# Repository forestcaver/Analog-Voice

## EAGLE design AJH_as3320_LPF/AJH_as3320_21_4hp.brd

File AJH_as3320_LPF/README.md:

# 3320 LPF

Built and tested

CC-BY-NC-SA 4.0

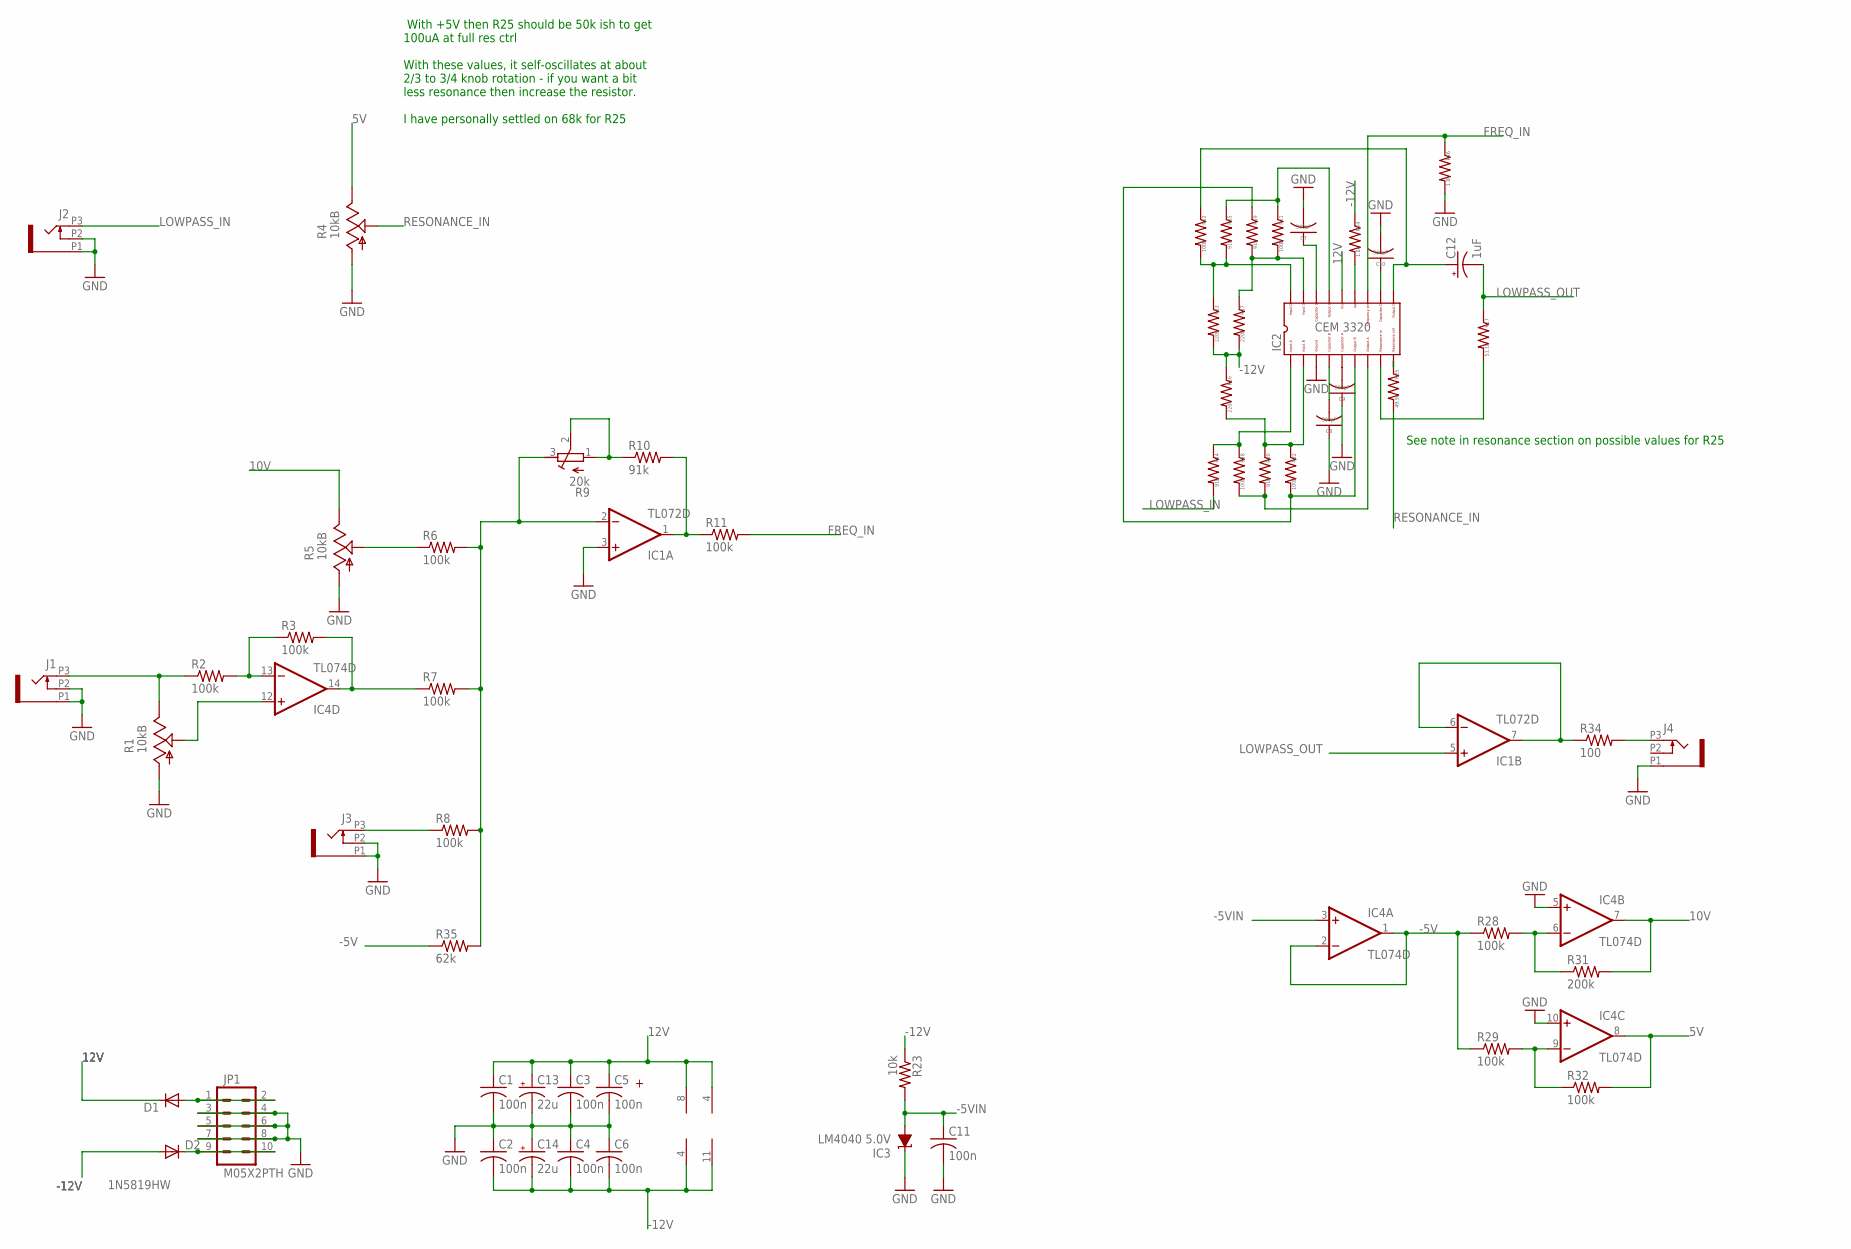
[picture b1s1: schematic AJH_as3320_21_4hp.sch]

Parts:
C1, C2, C3, C4, C5, C6, C11: 100n; C0603
C7, C8, C9, C10: 300pF; C0603
C12: 1uF; PANASONIC_B
C13, C14: 22u; PANASONIC_B
D1, D2: 1N5819HW; SOD123
IC1: TL072D; SO08
IC2: CEM3320QFN24; QFN24
IC3: LM4040 5.0V; DBZ_R-PDSO-G3
IC4: TL074D; SO14
J1, J2, J3, J4: PJ301_THONKICONN6; WQP_PJ_301M6
JP1: M05X2PTH; AVR_ICSP
R1, R4, R5: 10kB; ALPS_POT_VERTICAL
R2, R3, R6, R7, R8, R11, R12, R18, R21, R22, R28, R29, R32: 100k; R0603
R9: 20k; RTRIM3296X
R10, R14, R15, R19, R20: 91k; R0603
R13, R16, R17: 220k; R0603
R23: 10k; R0603
R24, R26: 1.8k; R0603
R25: 49.9k; R0603
R27: 51.1k; R0603
R31: 200k; R0603
R34: 100; R0603
R35: 62k; R0603

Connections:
5V: IC4.8 (OUT), R4.P$1 (E), R32.2
10V: IC4.7 (OUT), R5.P$1 (E), R31.2
12V: C1.1, C3.1, C5.1, C13.+, D1.C, IC1.8 (V+), IC2.P$22 (14), IC4.4 (V+)
-5V: IC4.1 (OUT), IC4.2 (-IN), R28.1, R29.1, R35.1
-5VIN: C11.1, IC3.2 (A), IC4.3 (+IN), R23.2
-12V: C2.2, C4.2, C6.2, C14.-, D2.A, IC1.4 (V-), IC4.11 (V-), R13.2, R16.1, R17.2, R23.1, R24.1
FREQ_IN: IC2.P$19 (12), R11.2, R26.1
GND: C1.2, C2.1, C3.2, C4.1, C5.2, C6.1, C7.2, C8.1, C9.1, C10.2, C11.2, C13.-, C14.+, IC1.3 (+IN), IC2.P$7 (3), IC3.1 (C), IC4.5 (+IN), IC4.10 (+IN), J1.P1 (1), J1.P2 (2), J2.P1 (1), J2.P2 (2), J3.P1 (1), J3.P2 (2), J4.P1 (1), JP1.3, JP1.4, JP1.5, JP1.6, JP1.7, JP1.8, R1.P$3 (A), R4.P$3 (A), R5.P$3 (A), R26.2
LOWPASS_IN: J2.P3 (3), R14.2
LOWPASS_OUT: C12.-, IC1.5 (+IN), R27.1
unnamed: IC1.6 (-IN), IC1.7 (OUT), R34.1
unnamed: IC2.P$3 (18), R12.2, R13.1, R15.2
unnamed: IC4.12 (+IN), R1.P$2 (S)
unnamed: R5.P$2 (S), R6.1
unnamed: IC4.13 (-IN), R2.2, R3.1
unnamed: D1.A, JP1.1, JP1.2
unnamed: IC1.2 (-IN), R6.2, R7.2, R8.2, R9.3 (A), R35.2
unnamed: IC1.1 (OUT), R10.2, R11.1
unnamed: J3.P3 (3), R8.1
unnamed: J4.P3 (3), R34.2
unnamed: IC4.14 (OUT), R3.2, R7.1
unnamed: IC4.9 (-IN), R29.2, R32.1
unnamed: IC4.6 (-IN), R28.2, R31.1
unnamed: D2.C, JP1.9, JP1.10
unnamed: C7.1, IC2.P$24 (16)
unnamed: C8.2, IC2.P$8 (4)
unnamed: C9.2, IC2.P$9 (5)
unnamed: C10.1, IC2.P$17 (11)
unnamed: IC2.P$15 (9), R25.1
unnamed: IC2.P$4 (1), R14.1, R18.1
unnamed: IC2.P$12 (7), R18.2, R20.2
unnamed: IC2.P$11 (6), R19.1, R22.2
unnamed: IC2.P$23 (15), R15.1, R21.1
unnamed: C12.+, IC2.P$16 (10), R12.1
unnamed: IC2.P$14 (8), R27.2
unnamed: IC2.P$5 (2), R16.2, R20.1, R22.1
unnamed: IC2.P$2 (17), R17.1, R19.2, R21.2
unnamed: IC2.P$20 (13), R24.2
unnamed: R9.1 (E), R9.2 (S), R10.1
unnamed: J1.P3 (3), R1.P$1 (E), R2.1
RESONANCE_IN: R4.P$2 (S), R25.2

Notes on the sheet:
With +5V then R25 should be 50k ish to get 100uA at full res ctrl With these values, it self-oscillates at about 2/3 to 3/4 knob rotation - if you want a bit less resonance then increase the resistor. I have personally settled on 68k for R25
See note in resonance section on possible values for R25

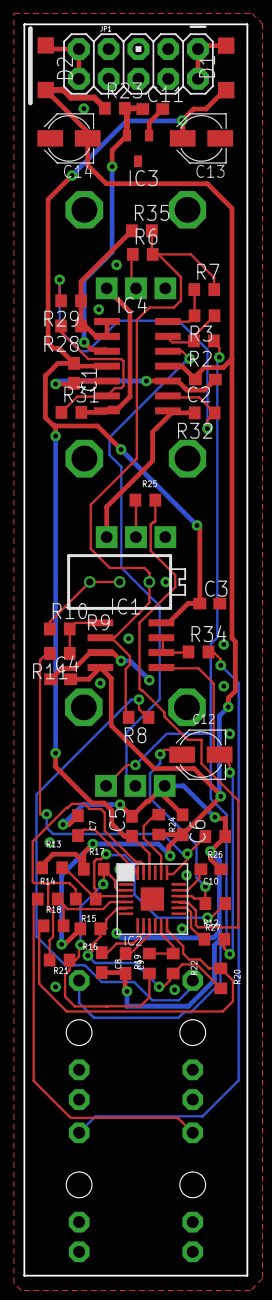
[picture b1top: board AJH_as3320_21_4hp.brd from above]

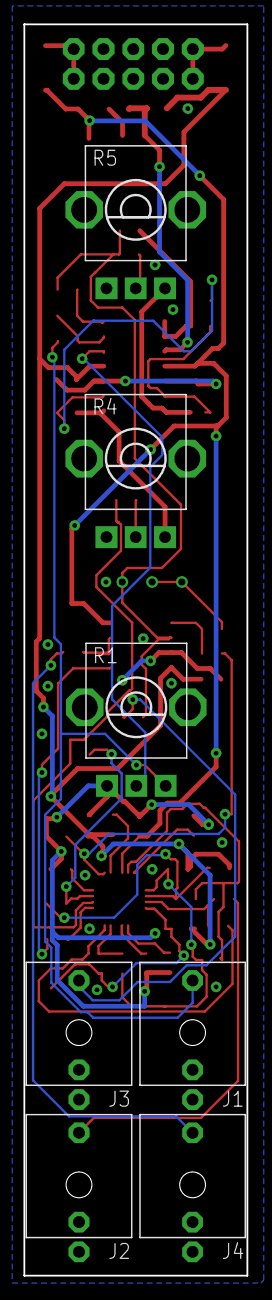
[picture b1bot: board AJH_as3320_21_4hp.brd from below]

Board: 2 copper layers, 19.0 x 106.8 mm, 58 parts (7 on the bottom side), 41 nets.

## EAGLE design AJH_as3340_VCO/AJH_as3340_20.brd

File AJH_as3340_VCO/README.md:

# 3340 VCO

Built and tested

CC-BY-NC-SA 4.0

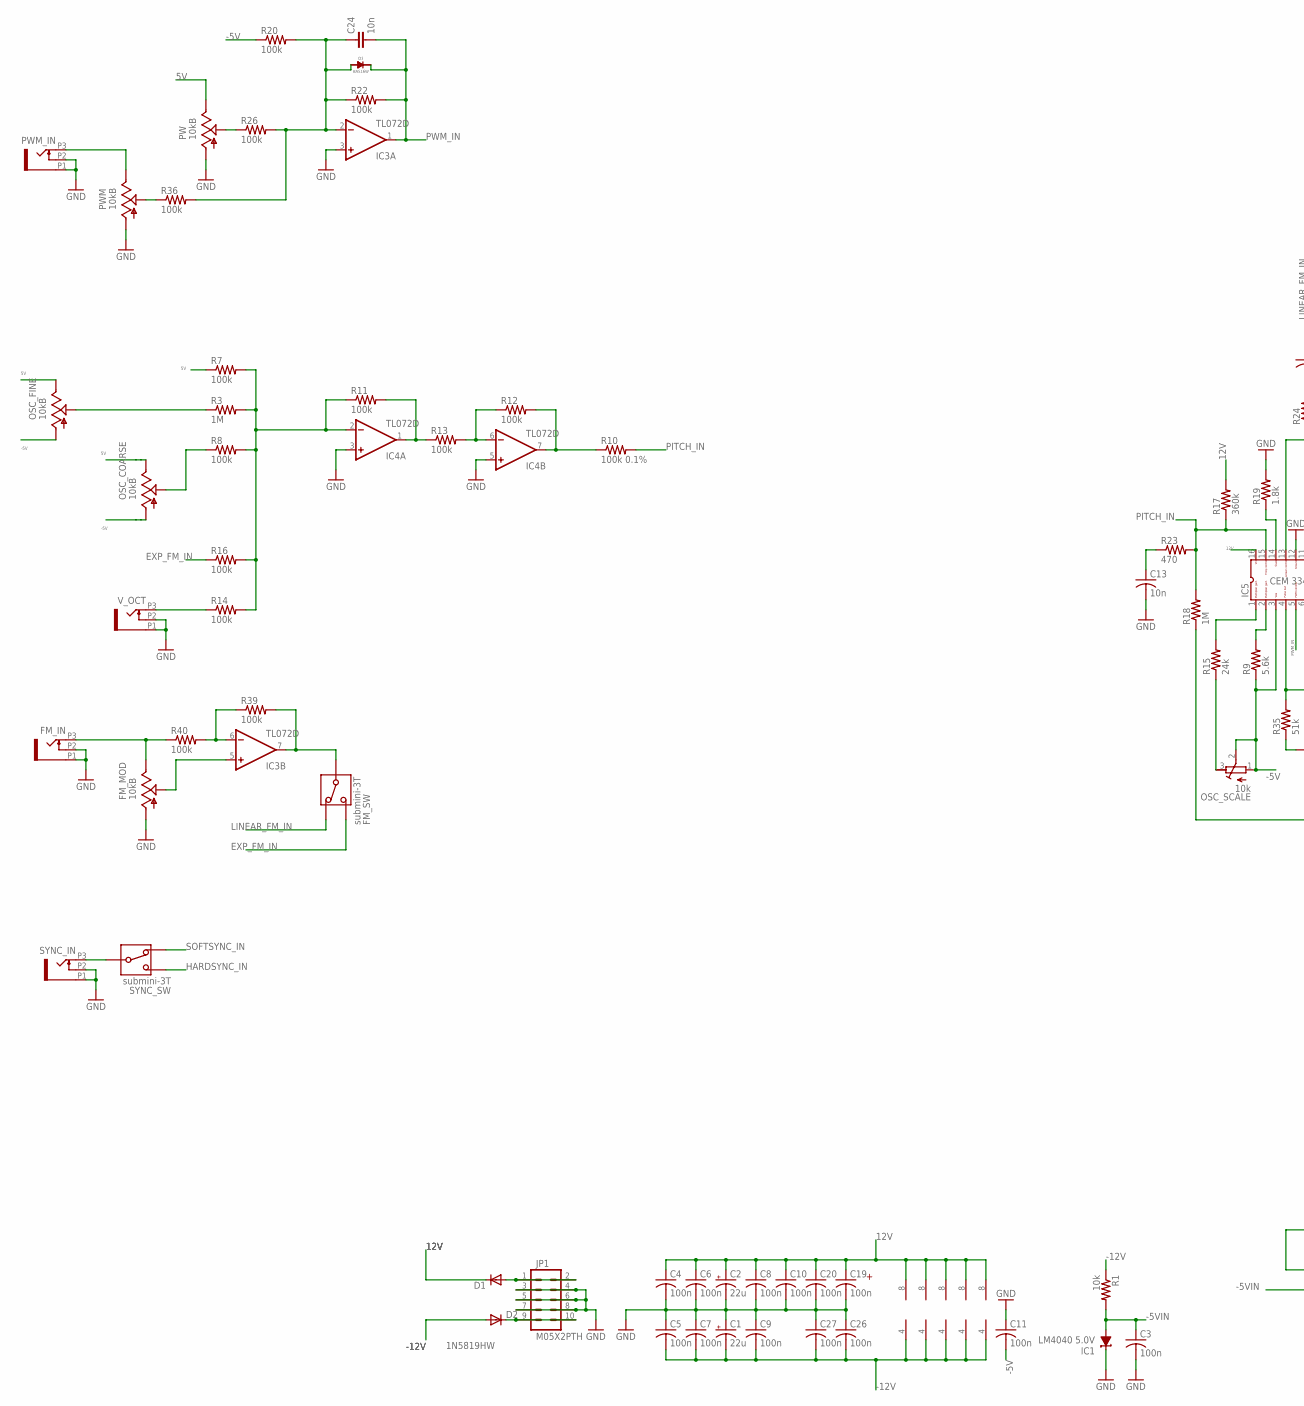
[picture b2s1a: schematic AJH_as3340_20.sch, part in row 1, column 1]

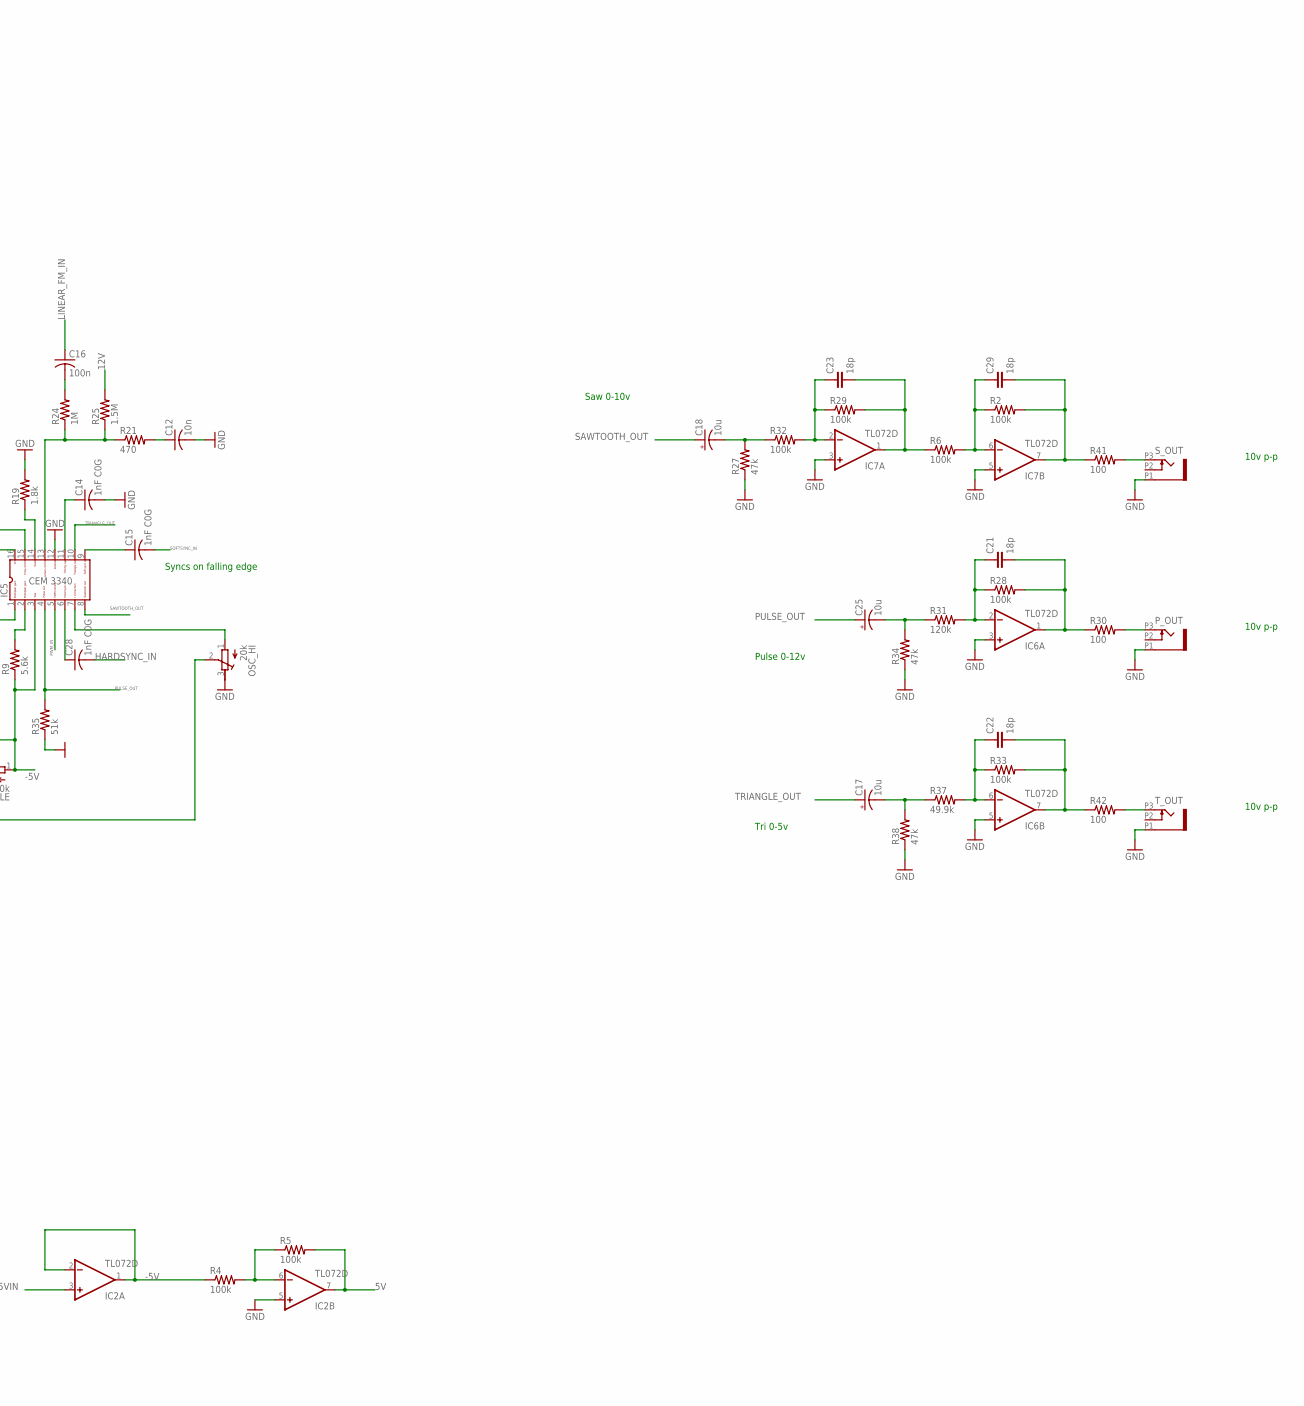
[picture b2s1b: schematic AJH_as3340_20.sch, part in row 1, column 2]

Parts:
C1, C2: 22u; PANASONIC_B
C3, C4, C5, C6, C7, C8, C9, C10, C11, C16, C19, C20, C26, C27: 100n; C0603
C12, C13, C24: 10n; C0603
C14, C15, C28: 1nF C0G; C0603
C17, C18, C25: 10u; PANASONIC_B
C21, C22, C23, C29: 18p; C0603
D1, D2: 1N5819HW; SOD123
D3: BAS16W; SOT-323
FM_IN: PJ301_THONKICONN6; WQP_PJ_301M6
FM_MOD: 10kB; ALPS_POT_VERTICAL_PS
FM_SW: submini-3T; SPDT-SUB
IC1: LM4040 5.0V; DBZ_R-PDSO-G3
IC2, IC3, IC4, IC6, IC7: TL072D; SO08
IC5: CEM3340SOIC16; SO16
JP1: M05X2PTH; AVR_ICSP
OSC_COARSE: 10kB; ALPS_POT_VERTICAL
OSC_FINE: 10kB; ALPS_POT_VERTICAL
OSC_HI: 20k; RTRIM3296X
OSC_SCALE: 10k; RTRIM3296X
PW: 10kB; ALPS_POT_VERTICAL_PS
PWM: 10kB; ALPS_POT_VERTICAL_PS
PWM_IN: PJ301_THONKICONN6; WQP_PJ_301M6
P_OUT: PJ301_THONKICONN6; WQP_PJ_301M6
R1: 10k; R0603
R2, R4, R5, R6, R7, R8, R11, R12, R13, R14, R16, R20, R22, R26, R28, R29, R32, R33, R36, R39, R40: 100k; R0603
R3, R18, R24: 1M; R0603
R9: 5.6k; R0603
R10: 100k 0.1%; R0603
R15: 24k; R0603
R17: 360k; R0603
R19: 1.8k; R0603
R21, R23: 470; R0603
R25: 1.5M; R0603
R27, R34, R38: 47k; R0603
R30, R41, R42: 100; R0603
R31: 120k; R0603
R35: 51k; R0603
R37: 49.9k; R0603
SYNC_IN: PJ301_THONKICONN6; WQP_PJ_301M6
SYNC_SW: submini-3T; SPDT-SUB
S_OUT: PJ301_THONKICONN6; WQP_PJ_301M6
T_OUT: PJ301_THONKICONN6; WQP_PJ_301M6
V_OCT: PJ301_THONKICONN6; WQP_PJ_301M6

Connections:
5V: IC2.7 (OUT), OSC_COARSE.P$1 (E), OSC_FINE.P$1 (E), PW.P$1 (E), R5.2, R7.1
12V: C2.+, C4.1, C6.1, C8.1, C10.1, C19.1, C20.1, D1.C, IC2.8 (V+), IC3.8 (V+), IC4.8 (V+), IC5.16, IC6.8 (V+), IC7.8 (V+), R17.2, R25.2
-5V: C11.2, IC2.1 (OUT), IC2.2 (-IN), IC5.3, OSC_COARSE.P$3 (A), OSC_FINE.P$3 (A), OSC_SCALE.1 (E), OSC_SCALE.2 (S), R4.1, R9.1, R20.1
-5VIN: C3.1, IC1.2 (A), IC2.3 (+IN), R1.2
-12V: C1.-, C5.2, C7.2, C9.2, C26.2, C27.2, D2.A, IC2.4 (V-), IC3.4 (V-), IC4.4 (V-), IC6.4 (V-), IC7.4 (V-), R1.1
EXP_FM_IN: FM_SW.P$1, R16.1
GND: C1.+, C2.-, C3.2, C4.2, C5.1, C6.2, C7.1, C8.2, C9.1, C10.2, C11.1, C12.2, C13.2, C14.2, C19.2, C20.2, C26.1, C27.1, FM_IN.P1 (1), FM_IN.P2 (2), FM_MOD.P$3 (A), IC1.1 (C), IC2.5 (+IN), IC3.3 (+IN), IC4.3 (+IN), IC4.5 (+IN), IC5.12, IC6.3 (+IN), IC6.5 (+IN), IC7.3 (+IN), IC7.5 (+IN), JP1.3, JP1.4, JP1.5, JP1.6, JP1.7, JP1.8, OSC_HI.3 (A), PW.P$3 (A), PWM.P$3 (A), PWM_IN.P1 (1), PWM_IN.P2 (2), P_OUT.P1 (1), R19.2, R27.1, R34.1, R35.1, R38.1, SYNC_IN.P1 (1), SYNC_IN.P2 (2), S_OUT.P1 (1), T_OUT.P1 (1), V_OCT.P1 (1), V_OCT.P2 (2)
HARDSYNC_IN: C28.2, SYNC_SW.P$1
LINEAR_FM_IN: C16.1, FM_SW.P$3
MAIN_CV1: PWM.P$1 (E), PWM_IN.P3 (3)
unnamed: PW.P$2 (S), R26.1
unnamed: R41.2, S_OUT.P3 (3)
unnamed: FM_MOD.P$2 (S), IC3.5 (+IN)
unnamed: OSC_COARSE.P$2 (S), R8.1
unnamed: IC3.6 (-IN), R39.1, R40.2
unnamed: D1.A, JP1.1, JP1.2
unnamed: IC4.2 (-IN), R3.2, R7.2, R8.2, R11.1, R14.2, R16.2
unnamed: IC4.1 (OUT), R11.2, R13.1
unnamed: IC4.6 (-IN), R12.1, R13.2
unnamed: R14.1, V_OCT.P3 (3)
unnamed: OSC_FINE.P$2 (S), R3.1
unnamed: FM_SW.P$2, IC3.7 (OUT), R39.2
unnamed: IC2.6 (-IN), R4.2, R5.1
unnamed: P_OUT.P3 (3), R30.2
unnamed: C29.1, IC7.6 (-IN), R2.1, R6.2
unnamed: R42.2, T_OUT.P3 (3)
unnamed: C18.-, R27.2, R32.1
unnamed: C25.-, R31.1, R34.2
unnamed: C17.-, R37.1, R38.2
unnamed: D2.C, JP1.9, JP1.10
unnamed: C23.1, IC7.2 (-IN), R29.1, R32.2
unnamed: C23.2, IC7.1 (OUT), R6.1, R29.2
unnamed: C21.2, IC6.1 (OUT), R28.2, R30.1
unnamed: C22.2, IC6.7 (OUT), R33.2, R42.1
unnamed: C22.1, IC6.6 (-IN), R33.1, R37.2
unnamed: C21.1, IC6.2 (-IN), R28.1, R31.2
unnamed: C15.1, IC5.9
unnamed: C13.1, R23.1
unnamed: OSC_HI.2 (S), R18.1
unnamed: IC5.1, R15.2
unnamed: OSC_SCALE.3 (A), R15.1
unnamed: IC5.2, R9.2
unnamed: IC5.14, R19.1
unnamed: C14.1, IC5.11
unnamed: C12.1, R21.2
unnamed: IC5.13, R21.1, R24.1, R25.1
unnamed: C16.2, R24.2
unnamed: C29.2, IC7.7 (OUT), R2.2, R41.1
unnamed: FM_IN.P3 (3), FM_MOD.P$1 (E), R40.1
unnamed: C28.1, IC5.6
unnamed: IC5.7, OSC_HI.1 (E)
unnamed: PWM.P$2 (S), R36.1
PITCH_IN: IC5.15, R10.2, R17.1, R18.2, R23.2
PRESUMMED_PITCH: IC4.7 (OUT), R10.1, R12.2
PULSE_OUT: C25.+, IC5.4, R35.2
PWM_2_IN_SUM: C24.1, D3.ANODE, IC3.2 (-IN), R20.2, R22.1, R26.2, R36.2
PWM_IN: C24.2, D3.CATHODE, IC3.1 (OUT), IC5.5, R22.2
SAWTOOTH_OUT: C18.+, IC5.8
SOFTSYNC_IN: C15.2, SYNC_SW.P$3
SYNC_IN: SYNC_IN.P3 (3), SYNC_SW.P$2
TRIANGLE_OUT: C17.+, IC5.10

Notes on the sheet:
10v p-p
Saw 0-10v
Pulse 0-12v
Tri 0-5v
Syncs on falling edge

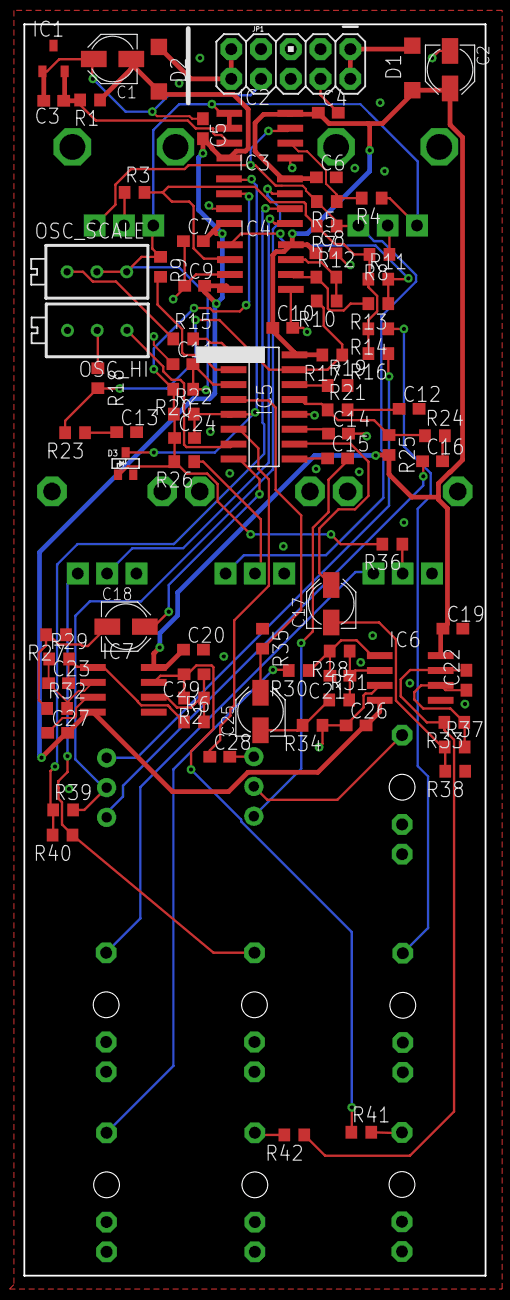
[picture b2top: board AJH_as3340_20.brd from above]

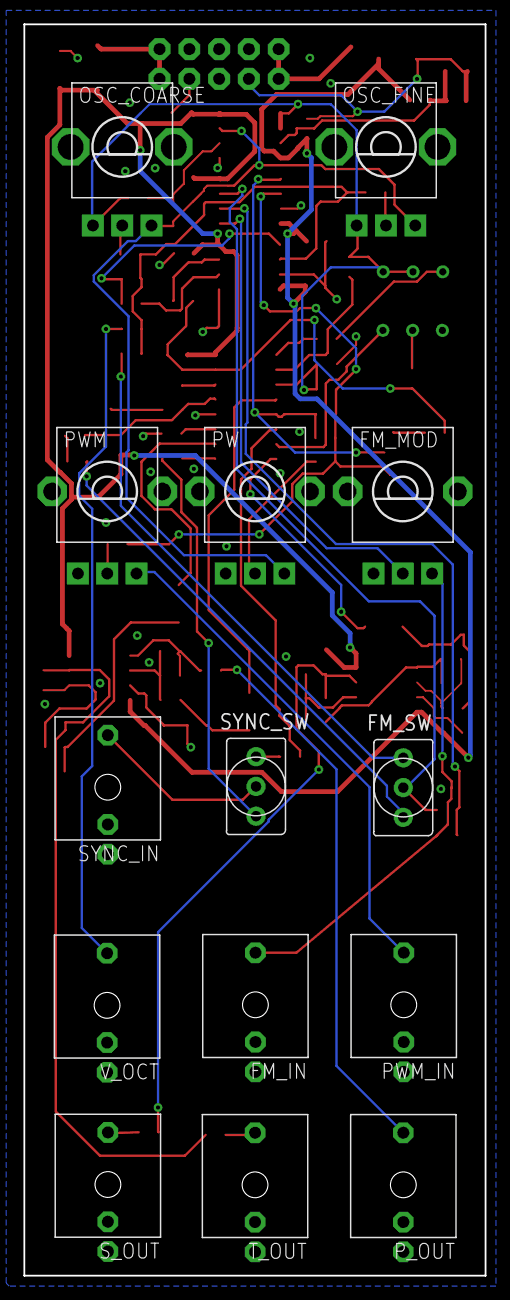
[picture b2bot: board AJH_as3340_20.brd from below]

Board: 2 copper layers, 39.4 x 106.8 mm, 98 parts (14 on the bottom side), 61 nets.

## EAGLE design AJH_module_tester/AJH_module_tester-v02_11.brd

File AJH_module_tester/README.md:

# Module Tester Module

Tested and working

CC-BY-SA 4.0

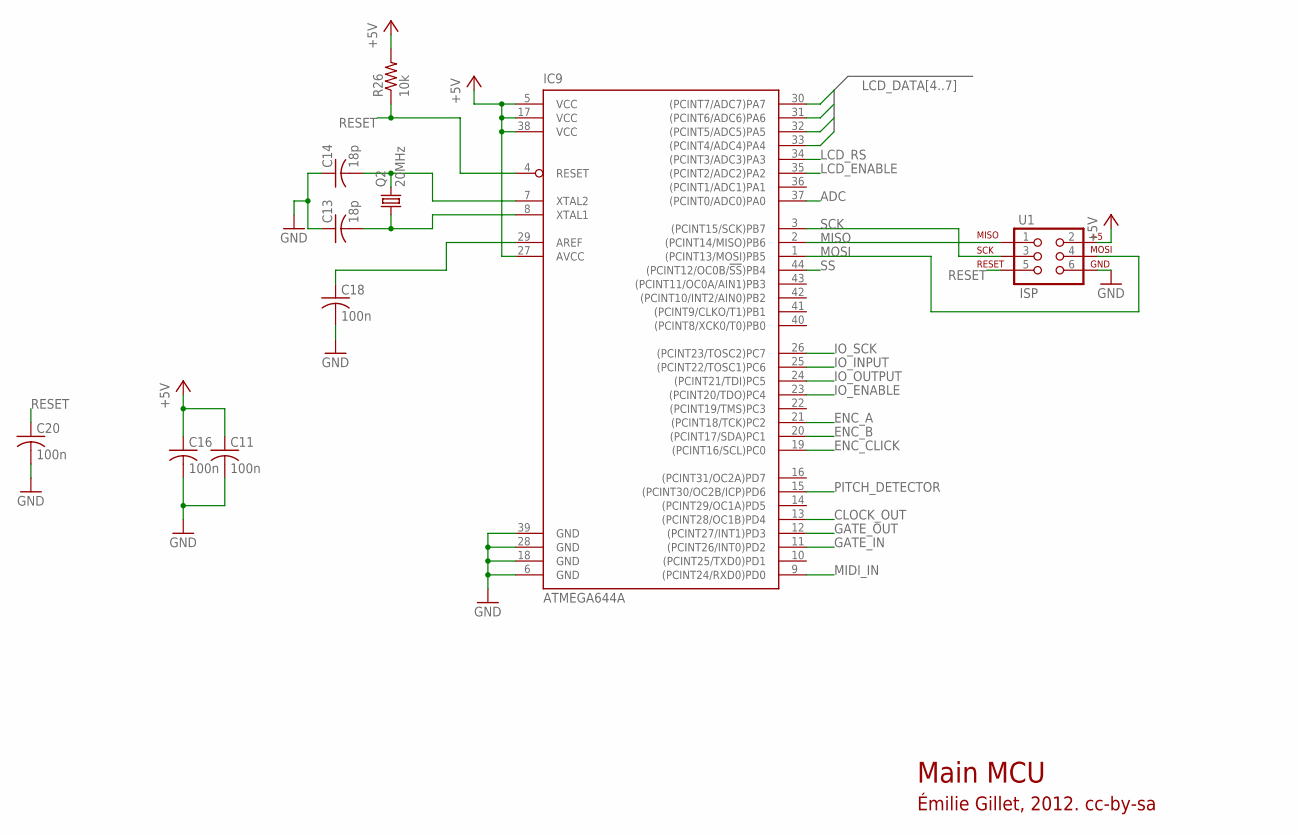
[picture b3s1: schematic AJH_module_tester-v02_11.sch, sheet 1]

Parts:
C11, C16, C18, C20: 100n; C0603
C13, C14: 18p; C0603
IC9: ATMEGA644A; TQFP44
Q2: 20MHz; HC49UP
R26: 10k; R0603
U1: ISP; 2X3

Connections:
+5V: C11.1, C16.1, IC9.5 (VCC), IC9.17 (VCC), IC9.27 (AVCC), IC9.38 (VCC), R26.2, U1.2; also elsewhere on the board
ADC: IC9.37 ((PCINT0/ADC0)PA0); also elsewhere on the board
CLOCK_OUT: IC9.13 ((PCINT28/OC1B)PD4); also elsewhere on the board
ENC_A: IC9.21 ((PCINT18/TCK)PC2); also elsewhere on the board
ENC_B: IC9.20 ((PCINT17/SDA)PC1); also elsewhere on the board
ENC_CLICK: IC9.19 ((PCINT16/SCL)PC0); also elsewhere on the board
GATE_IN: IC9.11 ((PCINT26/INT0)PD2); also elsewhere on the board
GATE_OUT: IC9.12 ((PCINT27/INT1)PD3); also elsewhere on the board
GND: C11.2, C13.1, C14.1, C16.2, C18.2, C20.2, IC9.6 (GND), IC9.18 (GND), IC9.28 (GND), IC9.39 (GND), U1.6; also elsewhere on the board
IO_ENABLE: IC9.23 ((PCINT20/TDO)PC4); also elsewhere on the board
IO_INPUT: IC9.25 ((PCINT22/TOSC1)PC6); also elsewhere on the board
IO_OUTPUT: IC9.24 ((PCINT21/TDI)PC5); also elsewhere on the board
IO_SCK: IC9.26 ((PCINT23/TOSC2)PC7); also elsewhere on the board
LCD_DATA4: IC9.33 ((PCINT4/ADC4)PA4); also elsewhere on the board
LCD_DATA5: IC9.32 ((PCINT5/ADC5)PA5); also elsewhere on the board
LCD_DATA6: IC9.31 ((PCINT6/ADC6)PA6); also elsewhere on the board
LCD_DATA7: IC9.30 ((PCINT7/ADC7)PA7); also elsewhere on the board
LCD_ENABLE: IC9.35 ((PCINT2/ADC2)PA2); also elsewhere on the board
LCD_RS: IC9.34 ((PCINT3/ADC3)PA3); also elsewhere on the board
MIDI_IN: IC9.9 ((PCINT24/RXD0)PD0); also elsewhere on the board
MISO: IC9.2 ((PCINT14/MISO)PB6), U1.1
MOSI: IC9.1 ((PCINT13/MOSI)PB5), U1.4; also elsewhere on the board
unnamed: C13.2, IC9.8 (XTAL1), Q2.1
unnamed: C14.2, IC9.7 (XTAL2), Q2.2
unnamed: C18.1, IC9.29 (AREF)
PITCH_DETECTOR: IC9.15 ((PCINT30/OC2B/ICP)PD6); also elsewhere on the board
RESET: C20.1, IC9.4 (RESET), R26.1, U1.5
SCK: IC9.3 ((PCINT15/SCK)PB7), U1.3; also elsewhere on the board
SS: IC9.44 ((PCINT12/OC0B/!SS!)PB4); also elsewhere on the board

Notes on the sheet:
Main MCU
Émilie Gillet, 2012. cc-by-sa

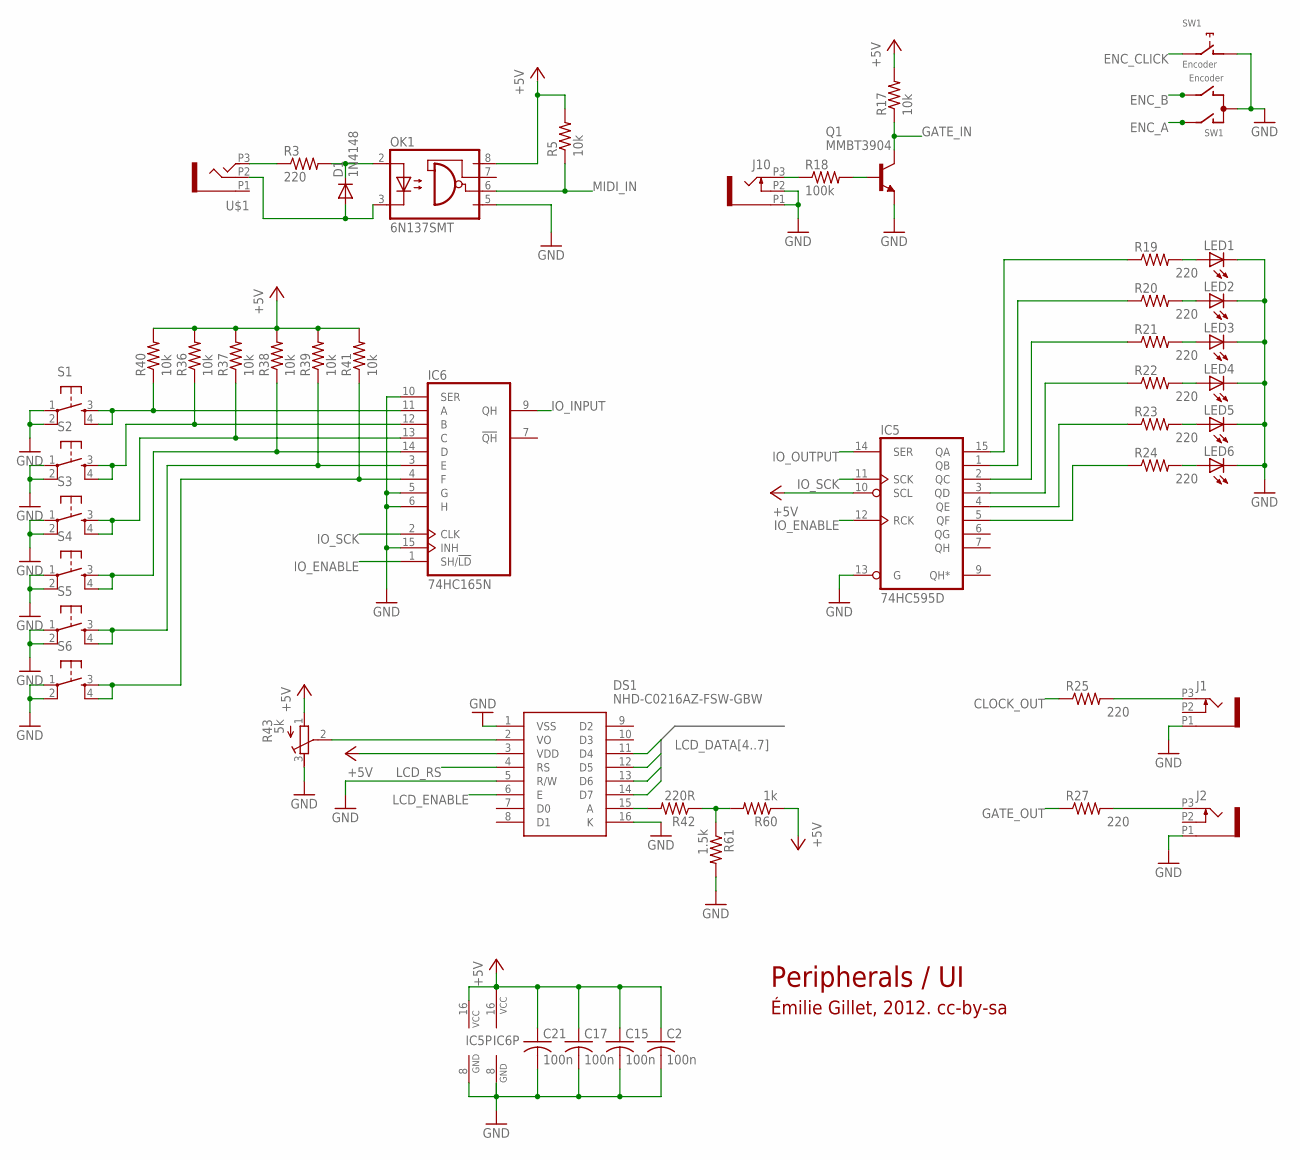
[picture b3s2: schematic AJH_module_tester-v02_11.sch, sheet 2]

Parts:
C2, C15, C17, C21: 100n; C0603
D1: 1N4148; SOD123
DS1: NHD-C0216AZ-FSW-GBW; NHDC0216AZFSWGBW
IC5: 74HC595D; SO16
IC6: 74HC165N; SO16
J1, J2, J10: PJ301_THONKICONN6; WQP_PJ_301M6
LED1, LED2, LED3, LED4, LED5, LED6: LED3MM
OK1: 6N137SMT; DIL8-SMD
Q1: MMBT3904; SOT23-BEC
R3, R19, R20, R21, R22, R23, R24, R25, R27: 220; R0603
R5, R17, R36, R37, R38, R39, R40, R41: 10k; R0603
R18: 100k; R0603
R42: 220R; R0603
R43: 5k; RTRIM3339P
R60: 1k; R0603
R61: 1.5k; R0603
S1, S2, S3, S4, S5, S6: TAC_SWITCHPTH; TACTILE-PTH
SW1: Encoder; ALPS_EC12E_SW
U$1: PJ366ST; WQP_PJ_301M8

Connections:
+5V: C2.1, C15.1, C17.1, C21.1, DS1.3 (VDD), IC5.10 (SCL), IC5.16 (VCC), IC6.16 (VCC), OK1.8 (VCC), R5.2, R17.2, R36.2, R37.2, R38.2, R39.2, R40.2, R41.2, R43.1 (E), R60.1; also elsewhere on the board
CLOCK_OUT: R25.1; also elsewhere on the board
ENC_A: SW1.A; also elsewhere on the board
ENC_B: SW1.B; also elsewhere on the board
ENC_CLICK: SW1.E (2); also elsewhere on the board
GATE_IN: Q1.C, R17.1; also elsewhere on the board
GATE_OUT: R27.1; also elsewhere on the board
GND: C2.2, C15.2, C17.2, C21.2, DS1.1 (VSS), DS1.5 (R/W), DS1.16 (K), IC5.8 (GND), IC5.13 (G), IC6.5 (G), IC6.6 (H), IC6.8 (GND), IC6.10 (SER), IC6.15 (INH), J1.P1 (1), J2.P1 (1), J10.P1 (1), J10.P2 (2), LED1.K (C), LED2.K (C), LED3.K (C), LED4.K (C), LED5.K (C), LED6.K (C), OK1.5 (GND), Q1.E, R43.3 (A), R61.2, S1.1, S1.2, S2.1, S2.2, S3.1, S3.2, S4.1, S4.2, S5.1, S5.2, S6.1, S6.2, SW1.C, SW1.D (1); also elsewhere on the board
IO_ENABLE: IC5.12 (RCK), IC6.1 (SH/!LD); also elsewhere on the board
IO_INPUT: IC6.9 (QH); also elsewhere on the board
IO_OUTPUT: IC5.14 (SER); also elsewhere on the board
IO_SCK: IC5.11 (SCK), IC6.2 (CLK); also elsewhere on the board
LCD_DATA4: DS1.11 (D4); also elsewhere on the board
LCD_DATA5: DS1.12 (D5); also elsewhere on the board
LCD_DATA6: DS1.13 (D6); also elsewhere on the board
LCD_DATA7: DS1.14 (D7); also elsewhere on the board
LCD_ENABLE: DS1.6 (E); also elsewhere on the board
LCD_RS: DS1.4 (RS); also elsewhere on the board
MIDI_IN: OK1.6 (VO), R5.1; also elsewhere on the board
unnamed: IC5.2 (QC), R21.1
unnamed: IC5.4 (QE), R23.1
unnamed: LED5.A, R23.2
unnamed: J10.P3 (3), R18.1
unnamed: R3.1, U$1.P3 (3)
unnamed: IC6.3 (E), R39.1, S5.3, S5.4
unnamed: J1.P3 (3), R25.2
unnamed: IC6.4 (F), R41.1, S6.3, S6.4
unnamed: IC6.14 (D), R38.1, S4.3, S4.4
unnamed: J2.P3 (3), R27.2
unnamed: LED6.A, R24.2
unnamed: IC5.5 (QF), R24.1
unnamed: IC6.11 (A), R40.1, S1.3, S1.4
unnamed: DS1.15 (A), R42.2
unnamed: D1.C, OK1.2 (A), R3.2
unnamed: IC5.15 (QA), R19.1
unnamed: IC5.1 (QB), R20.1
unnamed: IC5.3 (QD), R22.1
unnamed: DS1.2 (VO), R43.2 (S)
unnamed: LED1.A, R19.2
unnamed: LED2.A, R20.2
unnamed: LED3.A, R21.2
unnamed: LED4.A, R22.2
unnamed: R42.1, R60.2, R61.1
unnamed: Q1.B, R18.2
unnamed: D1.A, OK1.3 (C), U$1.P2 (2)
unnamed: IC6.12 (B), R36.1, S2.3, S2.4
unnamed: IC6.13 (C), R37.1, S3.3, S3.4

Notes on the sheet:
Peripherals / UI
Émilie Gillet, 2012. cc-by-sa

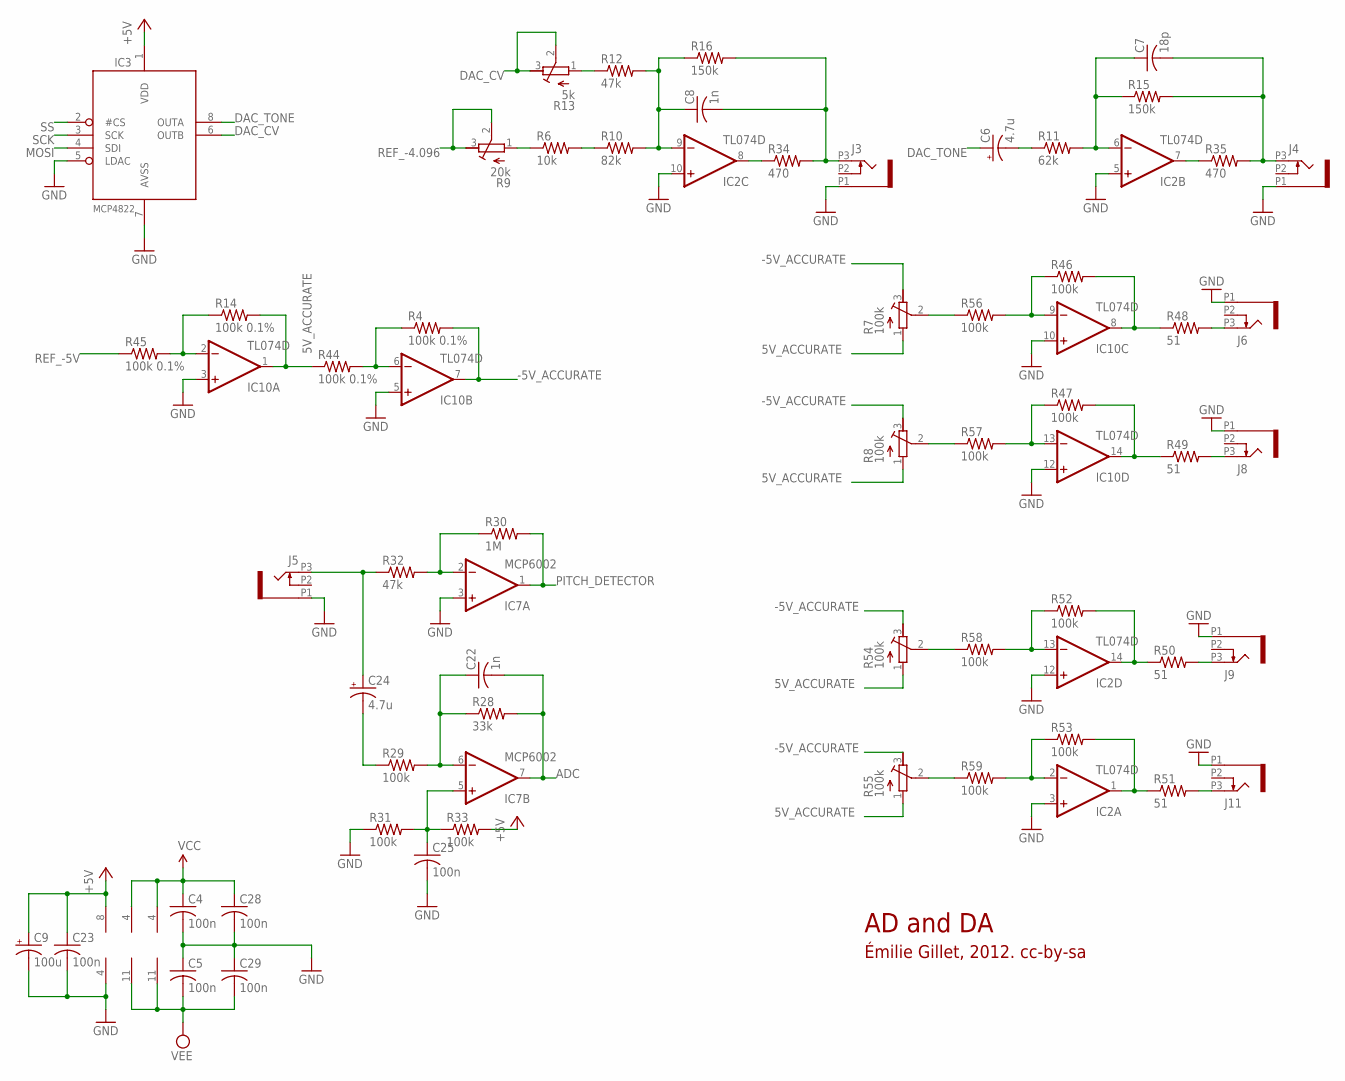
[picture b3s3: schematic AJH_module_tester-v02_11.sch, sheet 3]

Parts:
C4, C5, C23, C25, C28, C29: 100n; C0603
C6, C24: 4.7u; PANASONIC_A
C7: 18p; C0603
C8, C22: 1n; C0603
C9: 100u; PANASONIC_A
IC2, IC10: TL074D; SO14
IC3: MCP4822SO08; SO08
IC7: MCP6002; SO08
J3, J4, J5, J6, J8, J9, J11: PJ301_THONKICONN6; WQP_PJ_301M6
R4, R14, R44, R45: 100k 0.1%; R0603
R6: 10k; R0603
R7, R8, R54, R55: 100k; RTRIM3296W
R9: 20k; RTRIM3296W
R10: 82k; R0603
R11: 62k; R0603
R12, R32: 47k; R0603
R13: 5k; RTRIM3296W
R15, R16: 150k; R0603
R28: 33k; R0603
R29, R31, R33, R46, R47, R52, R53, R56, R57, R58, R59: 100k; R0603
R30: 1M; R0603
R34, R35: 470; R0603
R48, R49, R50, R51: 51; R0603

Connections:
5V_ACCURATE: IC10.1 (OUT), R7.1 (E), R8.1 (E), R14.2, R44.1, R54.1 (E), R55.1 (E)
+5V: C9.+, C23.1, IC3.1 (VDD), IC7.8 (V+), R33.2; also elsewhere on the board
-5V_ACCURATE: IC10.7 (OUT), R4.2, R7.3 (A), R8.3 (A), R54.3 (A), R55.3 (A)
ADC: C22.2, IC7.7 (OUT), R28.2; also elsewhere on the board
DAC_CV: IC3.6 (OUTB), R13.2 (S), R13.3 (A)
DAC_TONE: C6.+, IC3.8 (OUTA)
GND: C4.2, C5.1, C9.-, C23.2, C25.2, C28.2, C29.1, IC2.3 (+IN), IC2.5 (+IN), IC2.10 (+IN), IC2.12 (+IN), IC3.5 (LDAC), IC3.7 (AVSS), IC7.3 (+IN), IC7.4 (V-), IC10.3 (+IN), IC10.5 (+IN), IC10.10 (+IN), IC10.12 (+IN), J3.P1 (1), J4.P1 (1), J5.P1 (1), J6.P1 (1), J8.P1 (1), J9.P1 (1), J11.P1 (1), R31.1; also elsewhere on the board
MOSI: IC3.4 (SDI); also elsewhere on the board
unnamed: C24.+, J5.P3 (3), R32.1
unnamed: IC2.8 (OUT), R34.1
unnamed: IC2.7 (OUT), R35.1
unnamed: IC2.2 (-IN), R53.1, R59.2
unnamed: J8.P3 (3), R49.2
unnamed: C6.-, R11.1
unnamed: J6.P3 (3), R48.2
unnamed: C7.1, IC2.6 (-IN), R11.2, R15.1
unnamed: C8.2, J3.P3 (3), R16.2, R34.2
unnamed: C8.1, IC2.9 (-IN), R10.2, R12.2, R16.1
unnamed: R12.1, R13.1 (E)
unnamed: R6.1, R9.1 (E)
unnamed: R6.2, R10.1
unnamed: C25.1, IC7.5 (+IN), R31.2, R33.1
unnamed: IC7.2 (-IN), R30.1, R32.2
unnamed: C22.1, IC7.6 (-IN), R28.1, R29.2
unnamed: IC10.14 (OUT), R47.2, R49.1
unnamed: C24.-, R29.1
unnamed: IC2.14 (OUT), R50.1, R52.2
unnamed: IC10.9 (-IN), R46.1, R56.2
unnamed: IC10.8 (OUT), R46.2, R48.1
unnamed: IC10.13 (-IN), R47.1, R57.2
unnamed: IC10.2 (-IN), R14.1, R45.2
unnamed: IC10.6 (-IN), R4.1, R44.2
unnamed: IC2.13 (-IN), R52.1, R58.2
unnamed: R7.2 (S), R56.1
unnamed: J9.P3 (3), R50.2
unnamed: J11.P3 (3), R51.2
unnamed: IC2.1 (OUT), R51.1, R53.2
unnamed: R8.2 (S), R57.1
unnamed: R55.2 (S), R59.1
unnamed: R54.2 (S), R58.1
PITCH_DETECTOR: IC7.1 (OUT), R30.2; also elsewhere on the board
REF_-4.096: R9.2 (S), R9.3 (A); also elsewhere on the board
REF_-5V: R45.1; also elsewhere on the board
SCK: IC3.3 (SCK); also elsewhere on the board
SS: IC3.2 (#CS); also elsewhere on the board
TONE_OUT: C7.2, J4.P3 (3), R15.2, R35.2
VCC: C4.1, C28.1, IC2.4 (V+), IC10.4 (V+); also elsewhere on the board
VEE: C5.2, C29.2, IC2.11 (V-), IC10.11 (V-); also elsewhere on the board

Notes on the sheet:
AD and DA
Émilie Gillet, 2012. cc-by-sa
